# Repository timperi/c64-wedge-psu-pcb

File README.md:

# c64-wedge-psu-pcb

A replacement PCB for the C64 Wedge PSU.

This PCB is a direct replacement for the PCB in the “wedge” shaped C64 PSU. The old linear regulator, which often fails and can cause overvoltage, is replaced with a modern switching regulator. All components are through-hole.

## PCB layout (revisions 2.0 / 2.1)

The **KiCad PCB** was reworked for rev **2.0** (current silk **2.1**): **U1 (LM2576)** is placed **closer to the wedge middle wall** (the **inner** case wall along that edge of the PCB — not the outer wedge shell). That frees **vertical space** for the TO-220 **heatsink** and usually means **little or no lead forming** on the regulator compared to older layouts. Other parts were **rearranged** for clearance and assembly flow. **Silkscreen** shows **component values** (not only references) to make population easier. A **logo / graphic** is included on the board.

## Before you build

**Maintainer note:** Bench comparison (UBEC vs LM2576, ripple + temperatures, scope PNGs) is in **[`measurements/README.md`](measurements/README.md)**. Tagged **`v2.0.0`** is the **V2** design: PCB layout with room for a **TO-220 heatsink** on the LM2576—the fix for the thermal limitations of builds that could not fit a proper sink. **[Issue #4 — thermal capability and “3 A” marking](https://github.com/timperi/c64-wedge-psu-pcb/issues/4)** has the background on older layouts and realistic loads.

If you build from **older Gerbers or third‑party kits**, read Issue #4 first. Third‑party kits may not match the BOM here; treat any build as your own responsibility.

## Regulator and output voltage

The design uses **LM2576T-ADJ** with a classic feedback divider:

| Ref | Value   | Role |
| --- | ------- | ---- |
| **R1** | 1 kΩ   | FB to GND |
| **R2** | 3.3 kΩ | Regulated output (before the second-stage filter) to FB |

Nominal setpoint at the feedback node is about **5.29 V** (1.23 V × (1 + R2/R1)). That is intentionally a little above 5 V to offset load regulation, the drop across the second-stage inductor (L2 DCR), and cable loss, so the voltage at the C64 ends up closer to 5 V.

Feedback is taken **before** the output LC filter (L2 / C3), which is a common choice for stability with an extra post filter. **L2** and **C3** are **part of the intended build** (second-stage ripple filter); populate both unless you are deliberately experimenting with a modified topology. The voltage at the **+5VDC** pads can be slightly lower than the sensed node under heavy load because of L2 and trace resistance.

To target a different output, change **R1/R2** using the LM2576-ADJ divider relationship in the datasheet (e.g. closer to 5.0 V would use a lower R2 for the same R1).

## Optional parts

- **Power LED:** **LED1** with **R3** (220 Ω). Omit both if you do not want an indicator.

## Bench measurements

UBEC vs LM2576 **ripple** (Pk‑Pk @ 2 ms/div), **temperatures**, and **side‑by‑side scope captures**: **[`measurements/README.md`](measurements/README.md)**.

**Practical current guidance:** The LM2576 family is **rated** to **3 A**, and this board **can** be pushed there briefly, but **continuous 3 A is not recommended**. In the bench comparison (**case open**), at **3 A** the rail was **4.74 V** at the load and **air near the case vent** was **79 °C** (see **measurements/README**). That does **not** apply the same way when the **case is closed**; stagnant air and a warm transformer make things **worse**, not better.

For **continuous** use in a **closed** wedge with the **BOM heatsink**, **~2 A** is a realistic working ceiling. The comparison table in **measurements/** still lists **2.5 A** and **3 A** for the **open** bench data set, not as a **continuous** target in an enclosed PSU. A stock **C64** (often **~1.2 A** average) sits comfortably in the **~5 V** region with plenty of thermal margin when a **heatsink** is fitted as in the BOM.

---

**Project:** schematic and PCB rev **2.1** (title blocks in `c64-wedge-psu-pcb.kicad_sch` / `c64-wedge-psu-pcb.kicad_pcb`). BOM: `c64-wedge-psu-pcb-BOM.csv`.

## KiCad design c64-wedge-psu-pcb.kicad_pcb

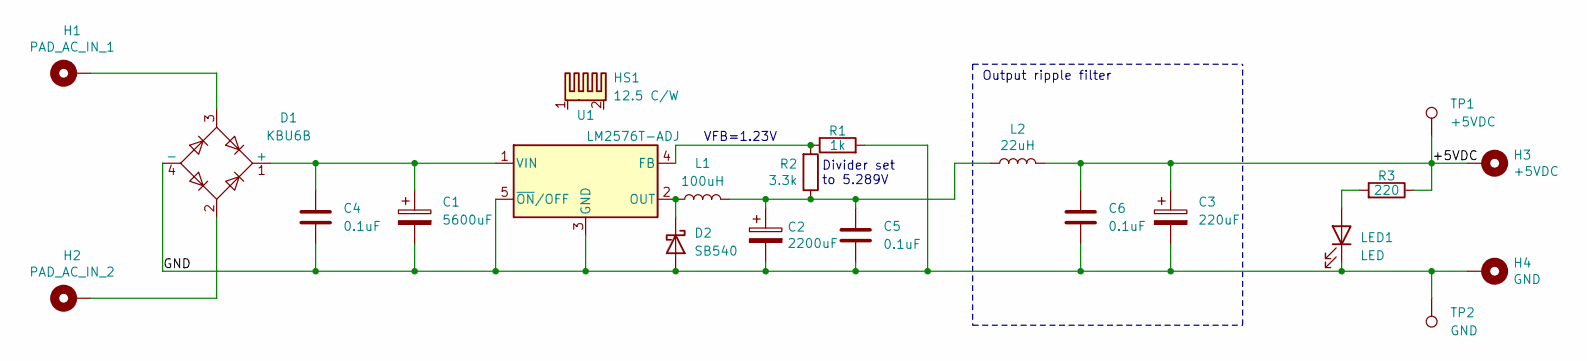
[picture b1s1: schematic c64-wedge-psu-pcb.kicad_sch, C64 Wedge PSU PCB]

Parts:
C1: 5600uF; CP_Radial_D16.0mm_P7.50mm
C2: 2200uF; CP_Radial_D16.0mm_P7.50mm
C3: 220uF; CP_Radial_D8.0mm_P3.50mm
C4, C5, C6: 0.1uF; C_Disc_D5.0mm_W2.5mm_P2.50mm
D1: KBU6B; Diode_Bridge_Vishay_KBU
D2: SB540; D_DO-201AD_P12.70mm_Horizontal
H1: PAD_AC_IN_1; SolderWire-1.5sqmm_1x01_D1.7mm_OD3.9mm
H2: PAD_AC_IN_2; SolderWire-1.5sqmm_1x01_D1.7mm_OD3.9mm
H3: +5VDC; SolderWire-1.5sqmm_1x01_D1.7mm_OD3.9mm
H4: GND; SolderWire-1.5sqmm_1x01_D1.7mm_OD3.9mm
HS1: 12.5 C/W; ATS-PCB1036
L1: 100uH; L_Toroid_Vertical_L24.6mm_W15.5mm_P11.44mm_Pulse_KM-4
L2: 22uH; Bourns-6100-220K-RC
LED1: LED; LED_D3.0mm
R1: 1k; R_Axial_DIN0207_L6.3mm_D2.5mm_P7.62mm_Horizontal
R2: 3.3k; R_Axial_DIN0207_L6.3mm_D2.5mm_P7.62mm_Horizontal
R3: 220; R_Axial_DIN0207_L6.3mm_D2.5mm_P7.62mm_Horizontal
TP1: +5VDC; TestPoint_THTPad_2.0x2.0mm_Drill1.0mm
TP2: GND; TestPoint_THTPad_2.0x2.0mm_Drill1.0mm
U1: LM2576T-ADJ; TO-220-5_P3.4x3.7mm_StaggerEven_Lead3.8mm_Vertical

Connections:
/+5VDC: C3.1, C6.1, H3.1, L2.2, R3.1, TP1.1
/GND: C1.2, C2.2, C3.2, C4.2, C5.2, C6.2, D1.4 (-), D2.2 (A), H4.1, LED1.1 (K), R1.2, TP2.1, U1.3 (GND), U1.5 (~ON/OFF)
unnamed: C2.1, C5.1, L1.2, L2.1, R2.1
unnamed: C1.1, C4.1, D1.1 (+), U1.1 (VIN)
unnamed: D1.2, H2.1
unnamed: D1.3, H1.1
unnamed: D2.1 (K), L1.1, U1.2 (OUT)
unnamed: LED1.2 (A), R3.2
unnamed: R1.1, R2.2, U1.4 (FB)

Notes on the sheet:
Output ripple filter
VFB=1.23V
Divider set to 5.289V

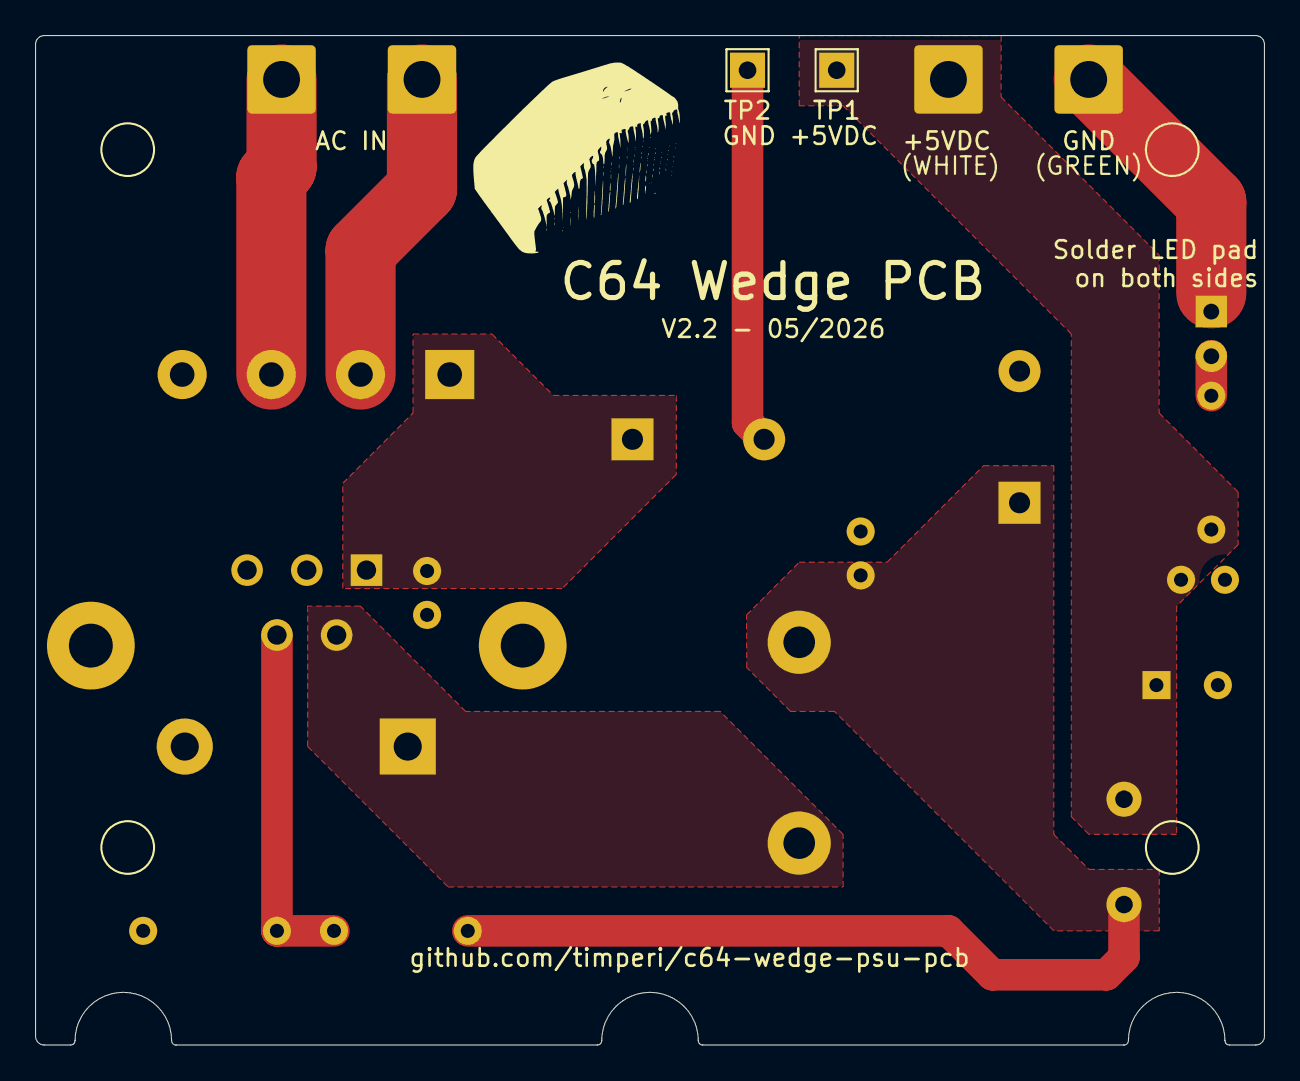
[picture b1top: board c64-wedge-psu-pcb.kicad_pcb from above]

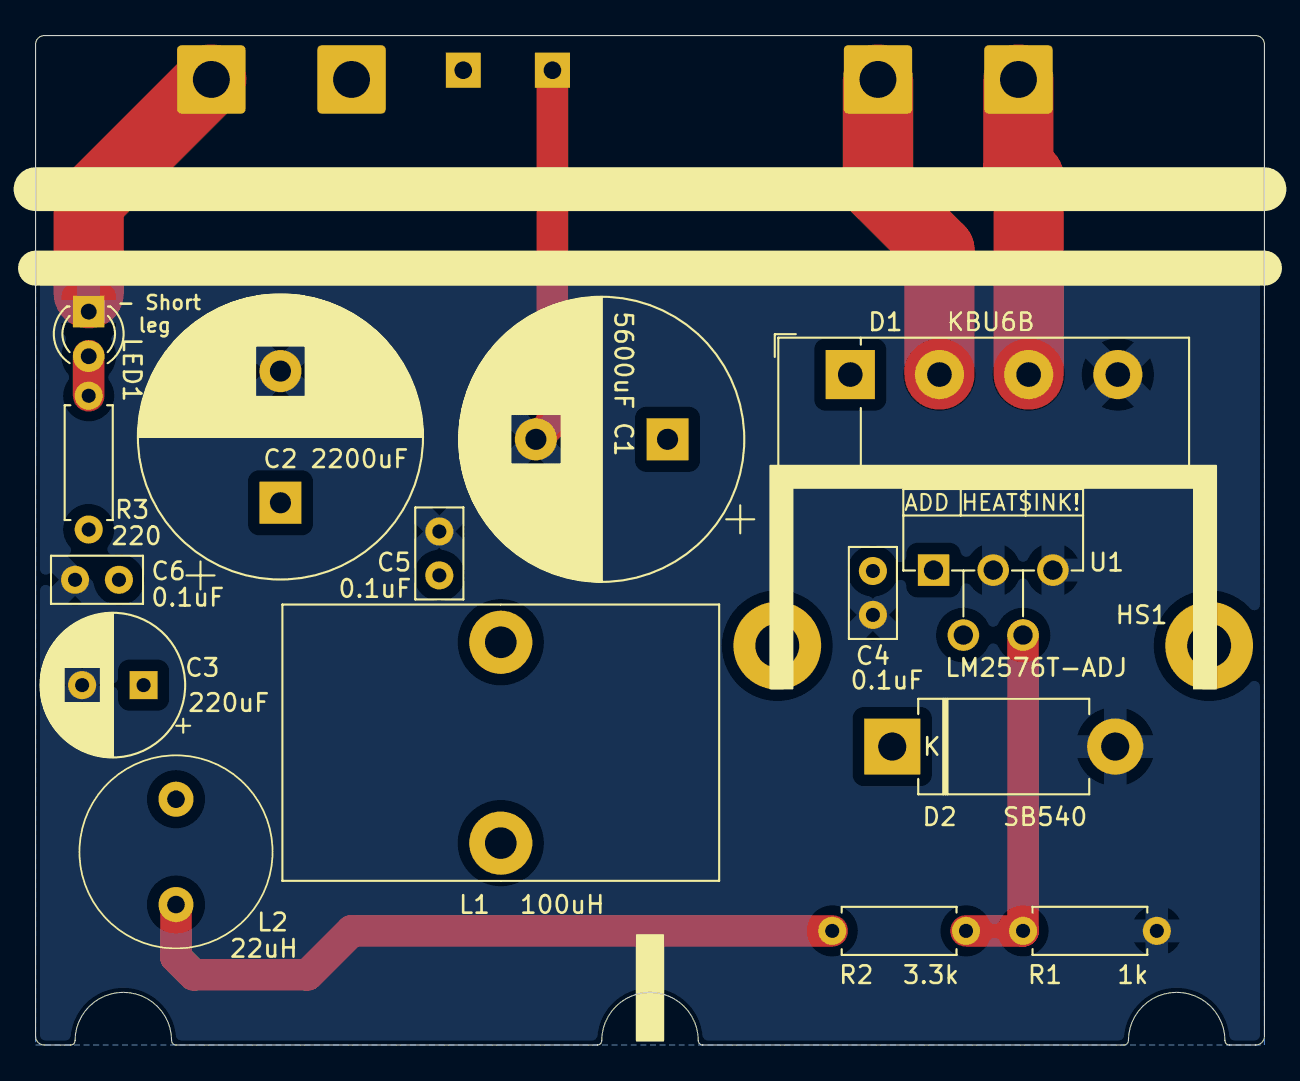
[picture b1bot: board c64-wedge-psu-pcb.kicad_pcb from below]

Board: 2 copper layers, 70.0 x 57.5 mm, 22 parts (16 on the bottom side), 9 nets.

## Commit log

2020-11-02 Create LICENSE
2020-11-02 Add files
2020-11-02 Make R1 pads bigger
2020-11-17 relayout, change some values and footprints
2020-11-21 Modify footprints, add some info text, modify resistor values
2020-11-21 Add images
2020-11-24 V1.1: Proper voltage divider to Feedback line. Make tracks wider. Some relayout. Update resistor values and L2 value.
2020-11-24 Update README.md
    Add some information and assembly instructions
2020-12-15 update resistor values
2020-12-15 add pics
2020-12-15 add scope images
2020-12-15 Add measurements to readme
2022-01-30 Fix feedback voltage divider (issue #1). Also change resitors to horizontal orientation.
2022-06-08 Adjust feedback voltage divider resitor values. Reposition led resistor, there is no room in previous position. Minor layout changes.
2024-09-14 Add (partial) BOM - might be wrong
2026-03-15 fixed
2026-03-15 Clean up: remove unused symbol libs, rescue, and legacy files
    - Remove rescue and project symbol libs from sym-lib-table (schematic uses global libs)
    - Delete c64-wedge-psu-pcb-rescue.kicad_sym, c64-wedge-psu-pcb.kicad_sym
    - Delete unused PE-53115.kicad_sym, KM-4.0.kicad_mod
    - Delete legacy c64-wedge-psu-pcb-cache.lib, .sch, .pro, .kicad_pcb-bak
2026-03-24 update ceramics with part number and update footprints
2026-03-29 Upgrade C1 to 5600uF and C2 to a better part, add some notes
2026-03-29 Add heatsink
2026-04-11 Add measurement checklist, README link to issue #4, schematic updates.
    Point builders to GitHub issue #4 before a tagged V2.0 release. Add a two-page printable bench checklist for ripple and load tests. Refresh the KiCad schematic (large file diff from editor save).
2026-04-11 PCB rev 2.0: docs, KiCad, gerbers, and release caveat
    README clarifies U1 placement against the wedge inner (middle) wall, documents bench results and BOM notes, and states that V2.0 will be tagged only after the latest board is built, verified, and re-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
    KiCad schematic/PCB/BOM refresh, wedge silk graphic footprint, wedge.gif, regenerated gerbers, and new gerber archive (replaces 2026-03-29 export).
2026-04-11 Docs: ripple measurements used 1× scope probe
    README bench paragraph and measurement checklist now state 1× probing (not 10×), matching the actual test setup.
2026-04-11 Docs: line ripple shots used 2 ms/div
    README and measurement checklist match the recorded scope setup (2 ms/div for 100 Hz envelope, ~two cycles on a 10-division graticule).
2026-04-11 PCB layout refresh, gerbers, measurements tree, UBEC memo
    KiCad schematic/PCB/project updates; regenerated gerbers and gerber zip (2026-04-12).
    Add measurements/ index with LM2576-rev2-e-load write-up, UBEC-2026-04-11 captures + README, historical-100us placeholder. README points to measurement pages.
    Add printable UBEC vs PCB comparison memo (docs). Remove old gerber-2026-04-11.zip.
2026-04-11 Add LM2576 heatsink theory calculator (Excel XML)
    Spreadsheet-style tool: theoretical buck + rectifier inputs, thermal stack (theta_jc/cs/sa), no measured data. Default matches BOM C1 and ATS-PCB1035 nominal C/W; open in Excel from .xml.
2026-04-13 Add .gitattributes; normalize KiCad files to LF
    Force LF for KiCad text formats. Renormalize affected tracked files only.
2026-04-13 Bump PCB/schematic revision to 2.1
    Title block rev 2.1 and silk version string V2.1. Includes minor KiCad save normalization (360° → 0° on a few text rotations).
2026-04-20 add latest measurements
2026-04-20 Docs: UBEC vs PCB V2.0 bench comparison in measurements/README
    Bench reference is measurements/README.md (table, setup, side-by-side PNGs under UBEC-2026-04-11/ and PCB-V2.0/). Root README points there; obsolete measurement docs, memos, checklist HTML, and lefto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
2026-04-20 PCB: move - Short leg silk inside board outline
2026-04-20 Docs: add load headings to measurement scope captures
2026-04-20 Update gerbers
2026-04-20 README: document v2.0.0 release and V2 heatsink fix
2026-04-22 README: ~2 A continuous ceiling for closed case; clarify open bench table
2026-05-04 PCB update for added 3D case
    added partial 3D model of the case (FreeCAD)
    added heatsink footprint
    added 3D model for some parts from the vendors
    changed rectifier to single component
    change board shape to fit snugly in the case
    moved some stuff around to make it fit in the available space
2026-05-06 Gitignore: ignore local workspace folders
